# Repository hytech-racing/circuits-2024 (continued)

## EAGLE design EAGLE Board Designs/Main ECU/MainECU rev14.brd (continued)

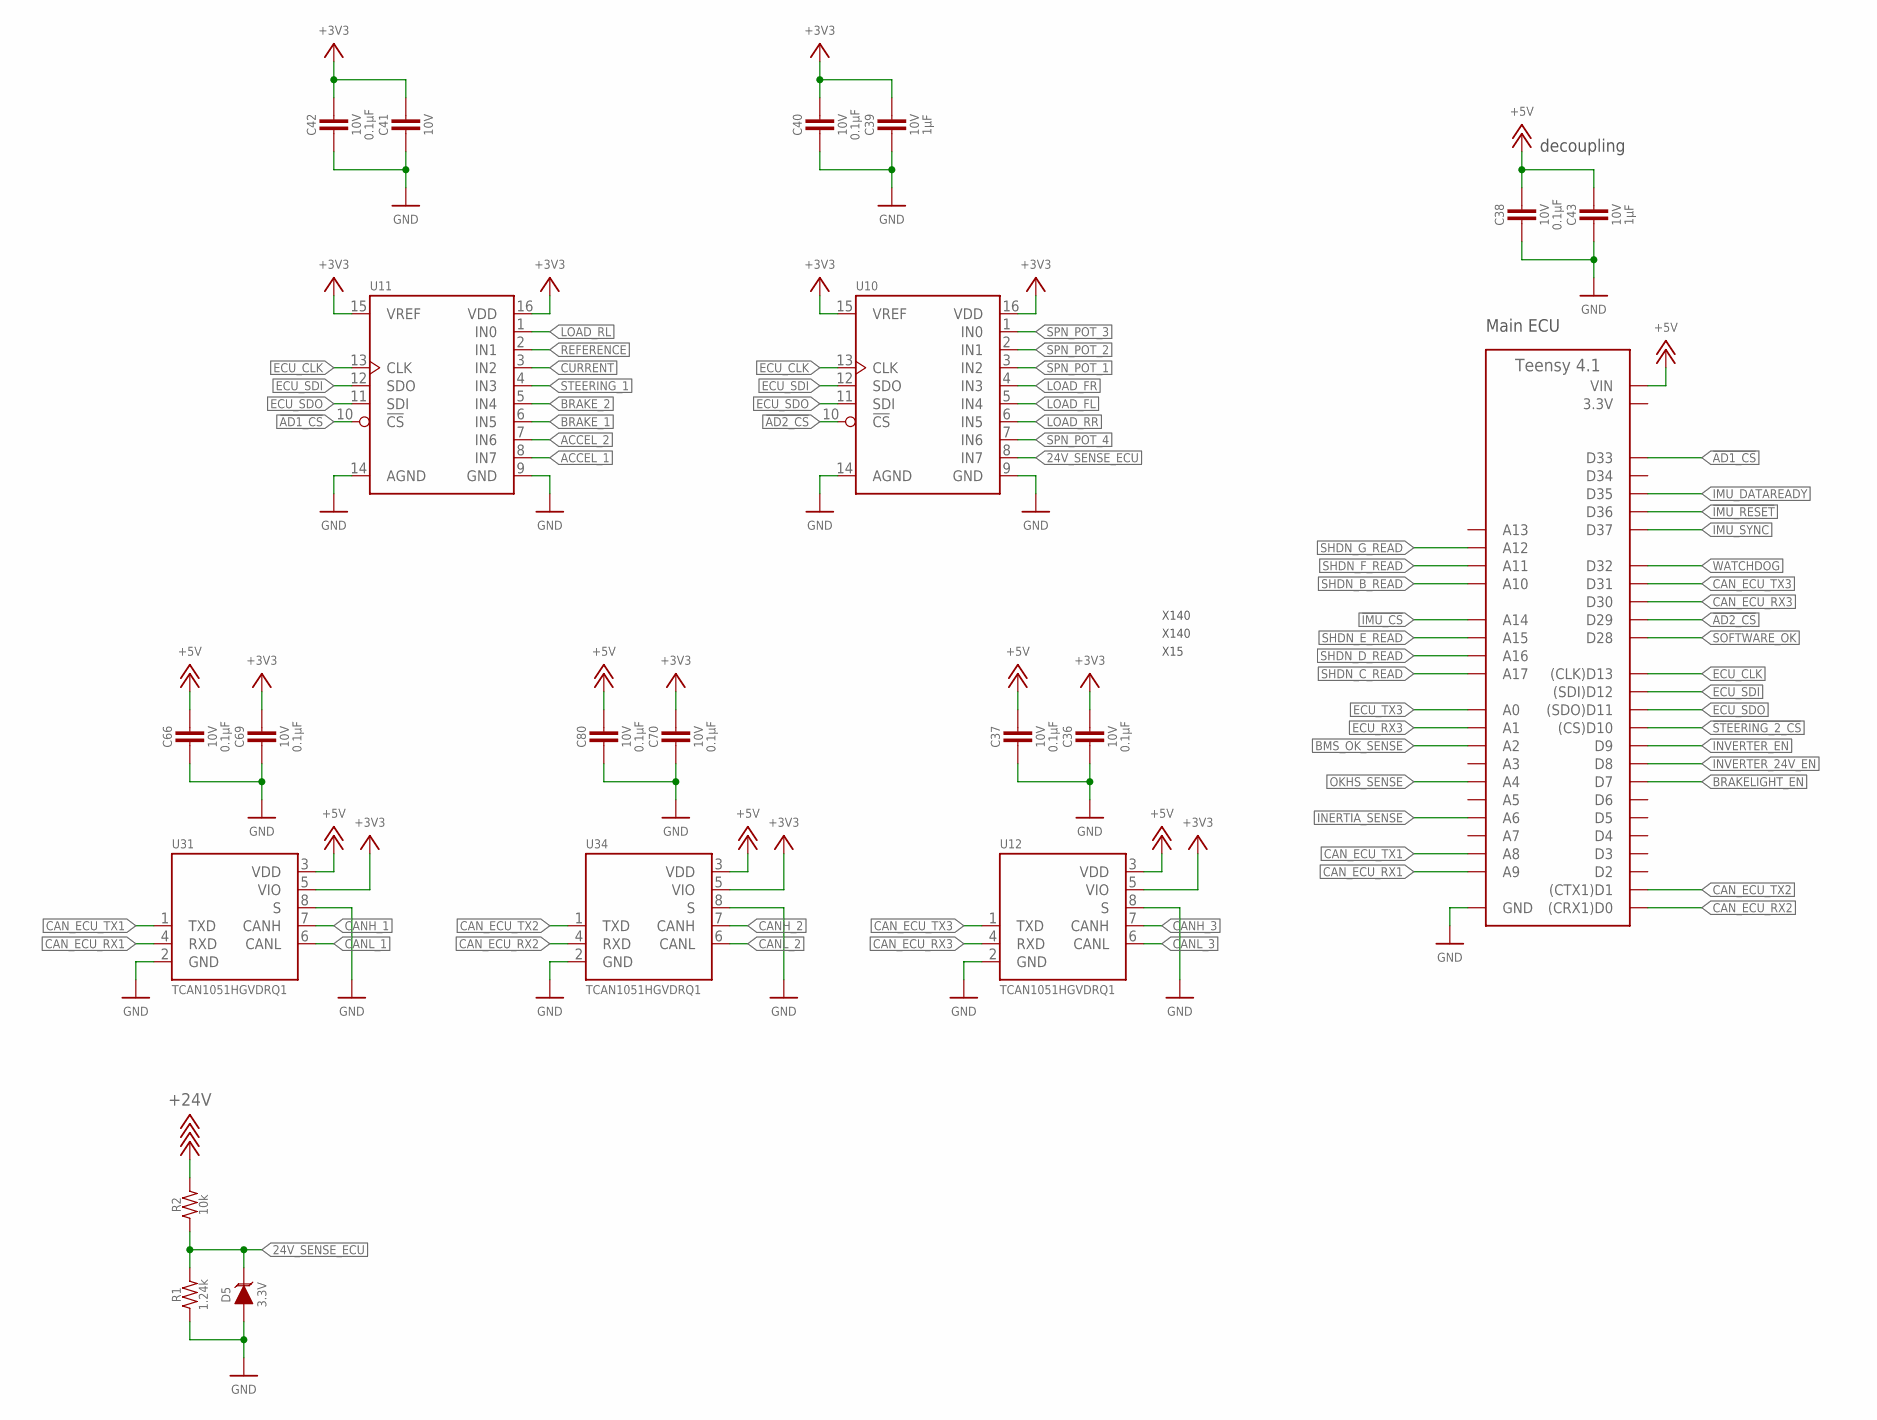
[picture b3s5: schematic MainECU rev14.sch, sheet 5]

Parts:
A2: TEENSY_4.1_SMT; TEENSY_LONG_SSM
C36, C37, C38, C40, C42, C66, C69, C70, C80: CAPACITOR_0603_10V_0.1UF; 0603-CAP
C39, C41, C43: CAPACITOR_0603_10V_1UF; 0603-CAP
D5: TVS__5V; SOT-23; VOLTAGE 3.3V; MPN GSOT03-E3-08
R1: RESISTOR_0603_1.24K; 0603-RES
R2: RESISTOR_0603_10K; 0603-RES
U10, U11: MCP3208; SOIC-16
U12, U31, U34: TCAN1051HQV-Q1; SOIC-08(NARROW,0.15")

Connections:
3.3V: A2.3.3V, A2.3.3V@1 (3.3V); also elsewhere on the board
24V_SENSE_ECU: D5.3 (C), R1.2, R2.1, U10.8 (IN7); also elsewhere on the board
!AD1_CS: A2.D33, U11.10 (!CS!)
!AD2_CS: A2.D29, U10.10 (!CS!)
!IMU_CS: A2.D38 (A14); also elsewhere on the board
!IMU_RESET: A2.D36; also elsewhere on the board
!STEERING_2_CS: A2.D10 ((CS)D10); also elsewhere on the board
+3V3: C36.1, C39.1, C40.1, C41.1, C42.1, C69.1, C70.1, U10.15 (VREF), U10.16 (VDD), U11.15 (VREF), U11.16 (VDD), U12.5 (VIO), U31.5 (VIO), U34.5 (VIO); also elsewhere on the board
+5V: A2.VIN, C37.1, C38.1, C43.1, C66.1, C80.1, U12.3 (VDD), U31.3 (VDD), U34.3 (VDD); also elsewhere on the board
+24V: R2.2; also elsewhere on the board
ACCEL_1: U11.8 (IN7); also elsewhere on the board
ACCEL_2: U11.7 (IN6); also elsewhere on the board
BMS_OK_SENSE: A2.D16 (A2); also elsewhere on the board
BRAKELIGHT_EN: A2.D7; also elsewhere on the board
BRAKE_1: U11.6 (IN5); also elsewhere on the board
BRAKE_2: U11.5 (IN4); also elsewhere on the board
CANH_1: U31.7 (CANH); also elsewhere on the board
CANH_2: U34.7 (CANH); also elsewhere on the board
CANH_3: U12.7 (CANH); also elsewhere on the board
CANL_1: U31.6 (CANL); also elsewhere on the board
CANL_2: U34.6 (CANL); also elsewhere on the board
CANL_3: U12.6 (CANL); also elsewhere on the board
CAN_ECU_RX1: A2.D23 (A9), U31.4 (RXD)
CAN_ECU_RX2: A2.D0 ((CRX1)D0), U34.4 (RXD)
CAN_ECU_RX3: A2.D30, U12.4 (RXD)
CAN_ECU_TX1: A2.D22 (A8), U31.1 (TXD)
CAN_ECU_TX2: A2.D1 ((CTX1)D1), U34.1 (TXD)
CAN_ECU_TX3: A2.D31, U12.1 (TXD)
CURRENT: U11.3 (IN2); also elsewhere on the board
ECU_CLK: A2.D13 ((CLK)D13), U10.13 (CLK), U11.13 (CLK); also elsewhere on the board
ECU_RX3: A2.D15 (A1); also elsewhere on the board
ECU_SDI: A2.D12 ((SDI)D12), U10.12 (SDO), U11.12 (SDO); also elsewhere on the board
ECU_SDO: A2.D11 ((SDO)D11), U10.11 (SDI), U11.11 (SDI); also elsewhere on the board
ECU_TX3: A2.D14 (A0); also elsewhere on the board
GND: A2.AGND/GND (GND), A2.GND, A2.GND@1 (GND), C36.2, C37.2, C38.2, C39.2, C40.2, C41.2, C42.2, C43.2, C66.2, C69.2, C70.2, C80.2, D5.1 (A), R1.1, U10.14 (AGND), U11.14 (AGND), U12.2 (GND), U12.8 (S), U31.2 (GND), U31.8 (S), U34.2 (GND), U34.8 (S); also elsewhere on the board
IMU_DATAREADY: A2.D35; also elsewhere on the board
IMU_SYNC: A2.D37; also elsewhere on the board
INERTIA_SENSE: A2.D20 (A6); also elsewhere on the board
INVERTER_24V_EN: A2.D8; also elsewhere on the board
INVERTER_EN: A2.D9; also elsewhere on the board
LOAD_FL: U10.5 (IN4); also elsewhere on the board
LOAD_FR: U10.4 (IN3); also elsewhere on the board
LOAD_RL: U11.1 (IN0); also elsewhere on the board
LOAD_RR: U10.6 (IN5); also elsewhere on the board
OKHS_SENSE: A2.D18 (A4); also elsewhere on the board
REFERENCE: U11.2 (IN1); also elsewhere on the board
SHDN_B_READ: A2.D24 (A10); also elsewhere on the board
SHDN_C_READ: A2.D41 (A17); also elsewhere on the board
SHDN_D_READ: A2.D40 (A16); also elsewhere on the board
SHDN_E_READ: A2.D39 (A15); also elsewhere on the board
SHDN_F_READ: A2.D25 (A11); also elsewhere on the board
SHDN_G_READ: A2.D26 (A12); also elsewhere on the board
SOFTWARE_OK: A2.D28; also elsewhere on the board
SPN_POT_1: U10.3 (IN2); also elsewhere on the board
SPN_POT_2: U10.2 (IN1); also elsewhere on the board
SPN_POT_3: U10.1 (IN0); also elsewhere on the board
SPN_POT_4: U10.7 (IN6); also elsewhere on the board
STEERING_1: U11.4 (IN3); also elsewhere on the board
WATCHDOG: A2.D32; also elsewhere on the board

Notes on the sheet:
decoupling
Main ECU
X15
X140

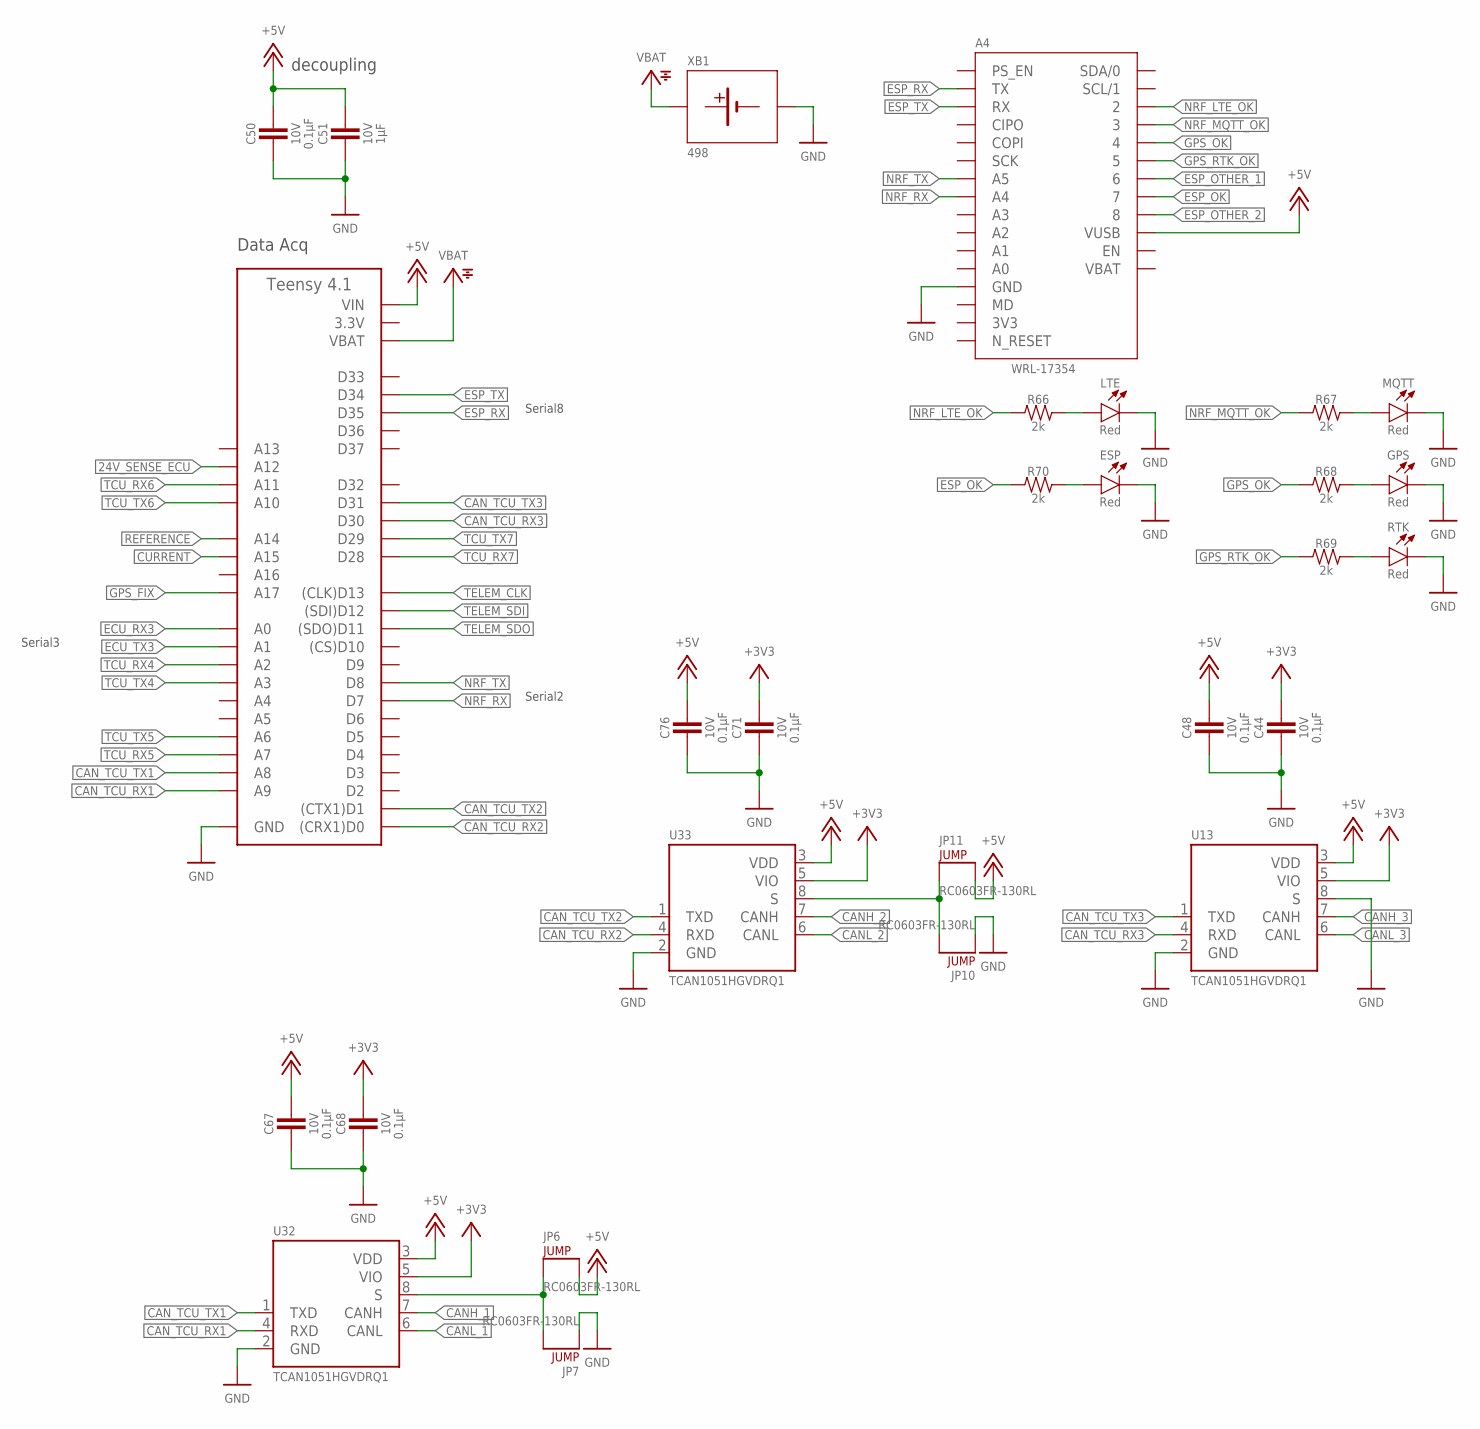
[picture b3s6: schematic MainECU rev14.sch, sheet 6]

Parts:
A3: TEENSY_4.1; TEENSY_LONG_EXT
A4: NRF9160LTE
C44, C48, C50, C67, C68, C71, C76: CAPACITOR_0603_10V_0.1UF; 0603-CAP
C51: CAPACITOR_0603_10V_1UF; 0603-CAP
ESP: LED_0603_RED; 0603-LED
GPS: LED_0603_RED; 0603-LED
JP6, JP11: JUMPER_0603_; 0603-RES
JP7, JP10: DNP; 0603-RES
LTE: LED_0603_RED; 0603-LED
MQTT: LED_0603_RED; 0603-LED
R66, R67, R68, R69, R70: RESISTOR_0603_2K; 0603-RES
RTK: LED_0603_RED; 0603-LED
U13, U32, U33: TCAN1051HQV-Q1; SOIC-08(NARROW,0.15")
XB1: BATTERY_HOLDER_KEYSTONE_498; 498

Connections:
3.3V: A3.3V3 (3.3V), A3.3V3@2 (3.3V), A3.3V3@3 (3.3V); also elsewhere on the board
3V3: A4.3V3
24V_SENSE_ECU: A3.D26 (A12); also elsewhere on the board
+3V3: C44.1, C68.1, C71.1, U13.5 (VIO), U32.5 (VIO), U33.5 (VIO); also elsewhere on the board
+5V: A3.VIN, A4.VUSB, C48.1, C50.1, C51.1, C67.1, C76.1, JP6.2, JP11.2, U13.3 (VDD), U32.3 (VDD), U33.3 (VDD); also elsewhere on the board
CANH_1: U32.7 (CANH); also elsewhere on the board
CANH_2: U33.7 (CANH); also elsewhere on the board
CANH_3: U13.7 (CANH); also elsewhere on the board
CANL_1: U32.6 (CANL); also elsewhere on the board
CANL_2: U33.6 (CANL); also elsewhere on the board
CANL_3: U13.6 (CANL); also elsewhere on the board
CAN_TCU_RX1: A3.D23 (A9), U32.4 (RXD)
CAN_TCU_RX2: A3.D0 ((CRX1)D0), U33.4 (RXD)
CAN_TCU_RX3: A3.D30, U13.4 (RXD)
CAN_TCU_TX1: A3.D22 (A8), U32.1 (TXD)
CAN_TCU_TX2: A3.D1 ((CTX1)D1), U33.1 (TXD)
CAN_TCU_TX3: A3.D31, U13.1 (TXD)
CURRENT: A3.D39 (A15); also elsewhere on the board
ECU_RX3: A3.D14 (A0); also elsewhere on the board
ECU_TX3: A3.D15 (A1); also elsewhere on the board
ESP_OK: A4.7, R70.1
ESP_OTHER_1: A4.6
ESP_OTHER_2: A4.8
ESP_RX: A3.D35, A4.TX
ESP_TX: A3.D34, A4.RX
GND: A3.AGND/GND (GND), A3.GND, A3.GND@2 (GND), A4.GND, C44.2, C48.2, C50.2, C51.2, C67.2, C68.2, C71.2, C76.2, ESP.1 (C), GPS.1 (C), JP7.1, JP10.1, LTE.1 (C), MQTT.1 (C), RTK.1 (C), U13.2 (GND), U13.8 (S), U32.2 (GND), U33.2 (GND), XB1.2 (MINUS); also elsewhere on the board
GPS_FIX: A3.D41 (A17)
GPS_OK: A4.4, R68.1
GPS_RTK_OK: A4.5, R69.1
unnamed: JP6.1, JP7.2, U32.8 (S)
unnamed: JP10.2, JP11.1, U33.8 (S)
unnamed: ESP.2 (A), R70.2
unnamed: LTE.2 (A), R66.2
unnamed: MQTT.2 (A), R67.2
unnamed: GPS.2 (A), R68.2
unnamed: R69.2, RTK.2 (A)
NRF_LTE_OK: A4.2, R66.1
NRF_MQTT_OK: A4.3, R67.1
NRF_RX: A3.D7, A4.A4
NRF_TX: A3.D8, A4.A5
REFERENCE: A3.D38 (A14); also elsewhere on the board
TCU_RX4: A3.D16 (A2)
TCU_RX5: A3.D21 (A7)
TCU_RX6: A3.D25 (A11)
TCU_RX7: A3.D28
TCU_TX4: A3.D17 (A3)
TCU_TX5: A3.D20 (A6)
TCU_TX6: A3.D24 (A10)
TCU_TX7: A3.D29
TELEM_CLK: A3.D13 ((CLK)D13)
TELEM_SDI: A3.D12 ((SDI)D12)
TELEM_SDO: A3.D11 ((SDO)D11)
VBAT: A3.VBAT, A4.VBAT, XB1.1 (PLUS)

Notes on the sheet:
decoupling
Data Acq
Serial2
Serial3
Serial8

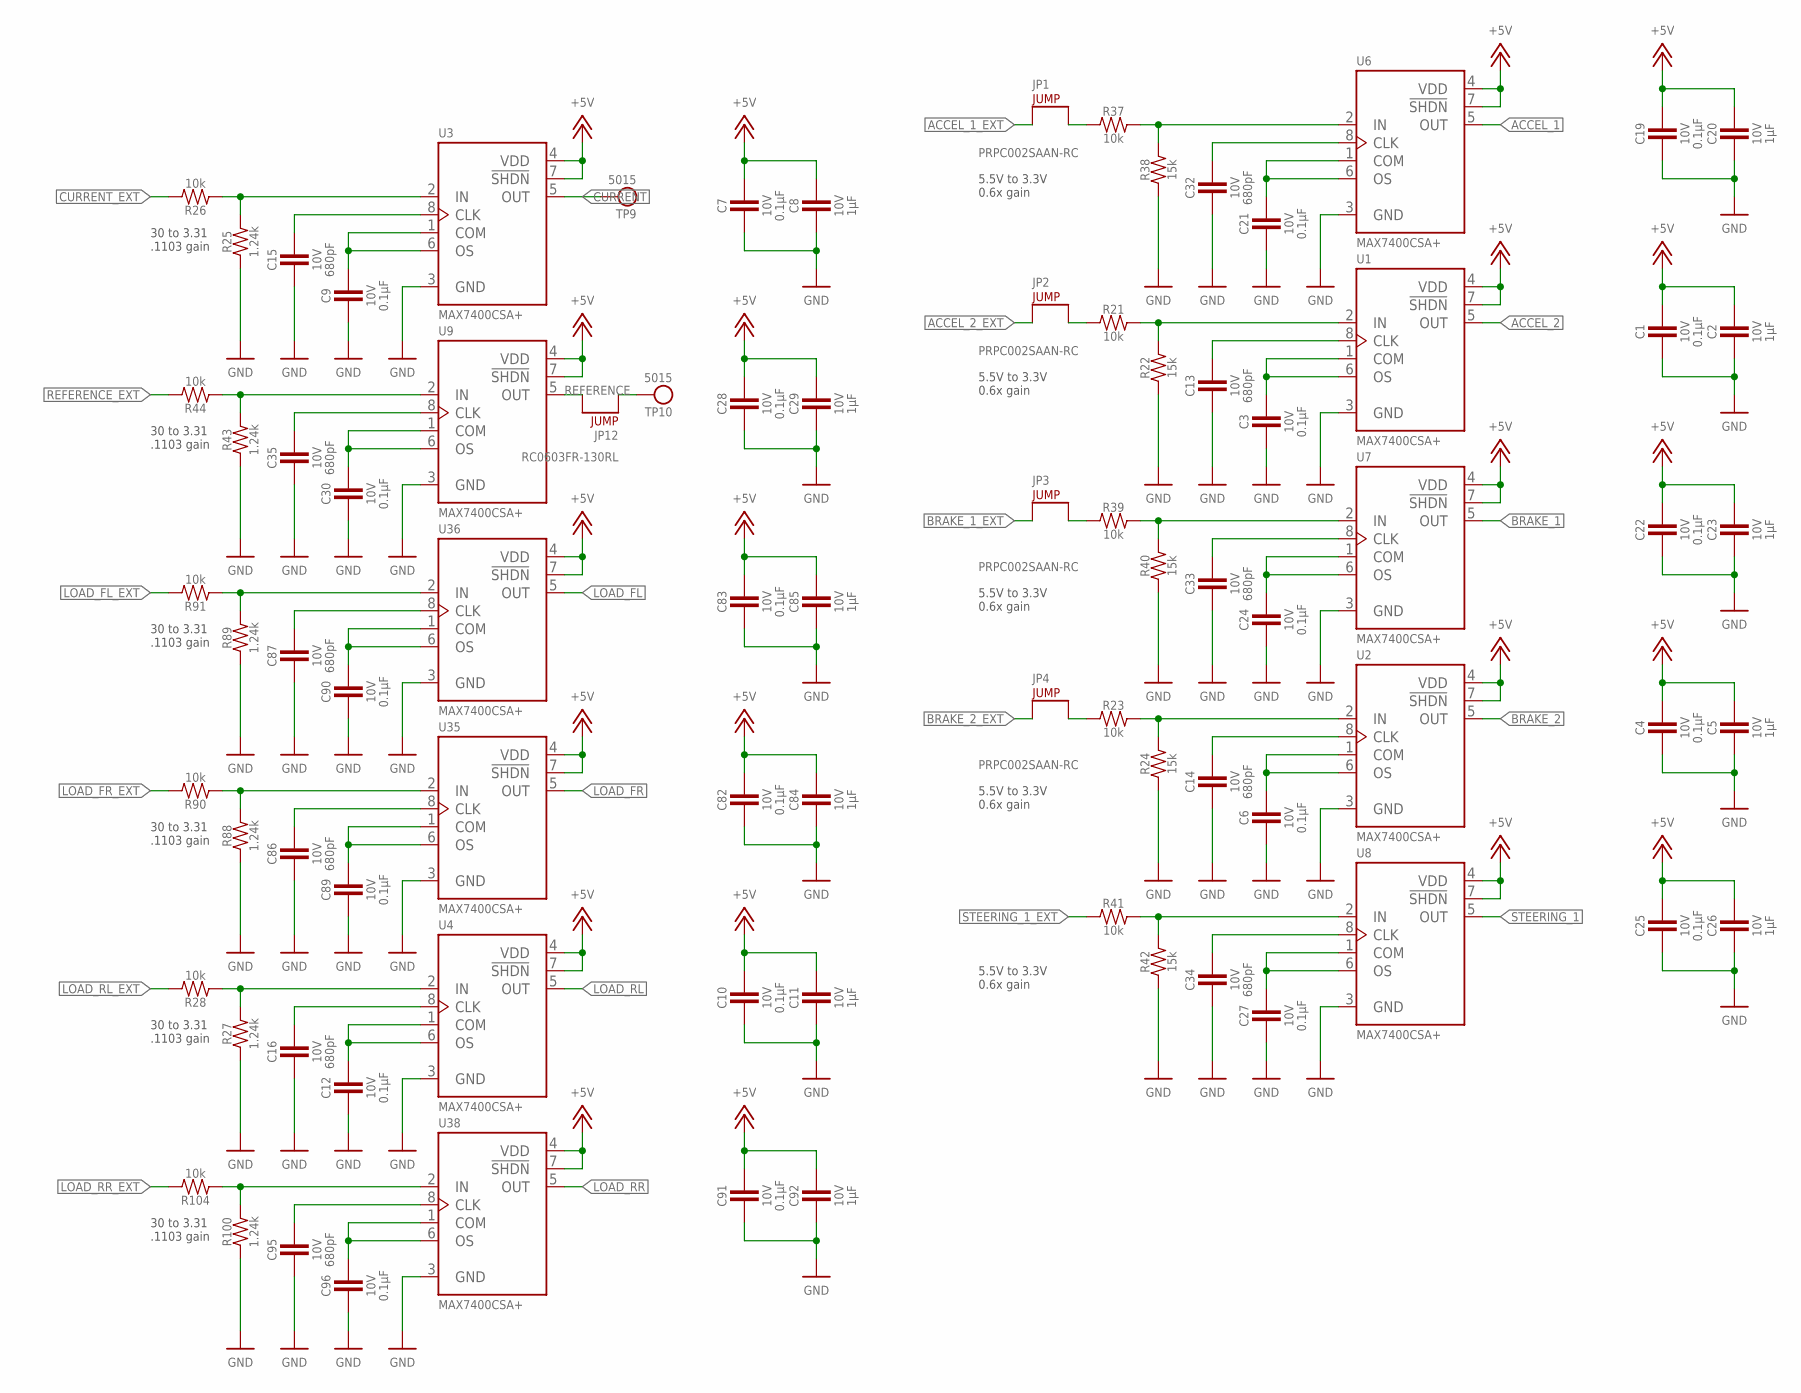
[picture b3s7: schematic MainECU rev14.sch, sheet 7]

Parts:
C1, C3, C4, C6, C7, C9, C10, C12, C19, C21, C22, C24, C25, C27, C28, C30, C82, C83, C89, C90, C91, C96: CAPACITOR_0603_10V_0.1UF; 0603-CAP
C2, C5, C8, C11, C20, C23, C26, C29, C84, C85, C92: CAPACITOR_0603_10V_1UF; 0603-CAP
C13, C14, C15, C16, C32, C33, C34, C35, C86, C87, C95: CAPACITOR_0603_10V_680PF; 0603-CAP
JP1, JP2, JP3, JP4: JUMPER__1X02; 1X02
JP12: JUMPER_0603_; 0603-RES
R21, R23, R26, R28, R37, R39, R41, R44, R90, R91, R104: RESISTOR_0603_10K; 0603-RES
R22, R24, R38, R40, R42: RESISTOR_0603_15K; 0603-RES
R25, R27, R43, R88, R89, R100: RESISTOR_0603_1.24K; 0603-RES
TP9, TP10: TEST_POINT; 5015
U1, U2, U3, U4, U6, U7, U8, U9, U35, U36, U38: MAX7400; SOIC-08(NARROW,0.15")

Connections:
+5V: C1.1, C2.1, C4.1, C5.1, C7.1, C8.1, C10.1, C11.1, C19.1, C20.1, C22.1, C23.1, C25.1, C26.1, C28.1, C29.1, C82.1, C83.1, C84.1, C85.1, C91.1, C92.1, U1.4 (VDD), U1.7 (!SHDN), U2.4 (VDD), U2.7 (!SHDN), U3.4 (VDD), U3.7 (!SHDN), U4.4 (VDD), U4.7 (!SHDN), U6.4 (VDD), U6.7 (!SHDN), U7.4 (VDD), U7.7 (!SHDN), U8.4 (VDD), U8.7 (!SHDN), U9.4 (VDD), U9.7 (!SHDN), U35.4 (VDD), U35.7 (!SHDN), U36.4 (VDD), U36.7 (!SHDN), U38.4 (VDD), U38.7 (!SHDN); also elsewhere on the board
ACCEL_1: U6.5 (OUT); also elsewhere on the board
ACCEL_1_EXT: JP1.1; also elsewhere on the board
ACCEL_1_PRE: R37.2, R38.2, U6.2 (IN)
ACCEL_2: U1.5 (OUT); also elsewhere on the board
ACCEL_2_EXT: JP2.1; also elsewhere on the board
ACCEL_2_PRE: R21.2, R22.2, U1.2 (IN)
BRAKE_1: U7.5 (OUT); also elsewhere on the board
BRAKE_1_EXT: JP3.1; also elsewhere on the board
BRAKE_1_PRE: R39.2, R40.2, U7.2 (IN)
BRAKE_2: U2.5 (OUT); also elsewhere on the board
BRAKE_2_EXT: JP4.1; also elsewhere on the board
BRAKE_2_PRE: R23.2, R24.2, U2.2 (IN)
CURRENT: TP9.1, U3.5 (OUT); also elsewhere on the board
CURRENT_EXT: R26.2; also elsewhere on the board
GND: C1.2, C2.2, C3.2, C4.2, C5.2, C6.2, C7.2, C8.2, C9.2, C10.2, C11.2, C12.2, C13.2, C14.2, C15.2, C16.2, C19.2, C20.2, C21.2, C22.2, C23.2, C24.2, C25.2, C26.2, C27.2, C28.2, C29.2, C30.2, C32.2, C33.2, C34.2, C35.2, C82.2, C83.2, C84.2, C85.2, C86.2, C87.2, C89.2, C90.2, C91.2, C92.2, C95.2, C96.2, R22.1, R24.1, R25.1, R27.1, R38.1, R40.1, R42.1, R43.1, R88.1, R89.1, R100.1, U1.3 (GND), U2.3 (GND), U3.3 (GND), U4.3 (GND), U6.3 (GND), U7.3 (GND), U8.3 (GND), U9.3 (GND), U35.3 (GND), U36.3 (GND), U38.3 (GND); also elsewhere on the board
LOAD_FL: U36.5 (OUT); also elsewhere on the board
LOAD_FL_EXT: R91.2; also elsewhere on the board
LOAD_FR: U35.5 (OUT); also elsewhere on the board
LOAD_FR_EXT: R90.2; also elsewhere on the board
LOAD_RL: U4.5 (OUT); also elsewhere on the board
LOAD_RL_EXT: R28.2; also elsewhere on the board
LOAD_RR: U38.5 (OUT); also elsewhere on the board
LOAD_RR_EXT: R104.2; also elsewhere on the board
unnamed: JP1.2, R37.1
unnamed: JP2.2, R21.1
unnamed: JP4.2, R23.1
unnamed: JP3.2, R39.1
unnamed: JP12.2, U9.5 (OUT)
unnamed: R25.2, R26.1, U3.2 (IN)
unnamed: C9.1, U3.1 (COM), U3.6 (OS)
unnamed: C15.1, U3.8 (CLK)
unnamed: R43.2, R44.1, U9.2 (IN)
unnamed: C30.1, U9.1 (COM), U9.6 (OS)
unnamed: C35.1, U9.8 (CLK)
unnamed: R89.2, R91.1, U36.2 (IN)
unnamed: C90.1, U36.1 (COM), U36.6 (OS)
unnamed: C87.1, U36.8 (CLK)
unnamed: R88.2, R90.1, U35.2 (IN)
unnamed: C89.1, U35.1 (COM), U35.6 (OS)
unnamed: C86.1, U35.8 (CLK)
unnamed: R27.2, R28.1, U4.2 (IN)
unnamed: C12.1, U4.1 (COM), U4.6 (OS)
unnamed: C16.1, U4.8 (CLK)
unnamed: R100.2, R104.1, U38.2 (IN)
unnamed: C96.1, U38.1 (COM), U38.6 (OS)
unnamed: C95.1, U38.8 (CLK)
unnamed: C27.1, U8.1 (COM), U8.6 (OS)
unnamed: C21.1, U6.1 (COM), U6.6 (OS)
unnamed: C32.1, U6.8 (CLK)
unnamed: C34.1, U8.8 (CLK)
unnamed: C3.1, U1.1 (COM), U1.6 (OS)
unnamed: C13.1, U1.8 (CLK)
unnamed: C24.1, U7.1 (COM), U7.6 (OS)
unnamed: C33.1, U7.8 (CLK)
unnamed: C6.1, U2.1 (COM), U2.6 (OS)
unnamed: C14.1, U2.8 (CLK)
REFERENCE: JP12.1, TP10.1; also elsewhere on the board
REFERENCE_EXT: R44.2; also elsewhere on the board
STEERING_1: U8.5 (OUT); also elsewhere on the board
STEERING_1_EXT: R41.1; also elsewhere on the board
STEERING_1_PRE: R41.2, R42.2, U8.2 (IN)

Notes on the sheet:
30 to 3.31 .1103 gain
5.5V to 3.3V 0.6x gain

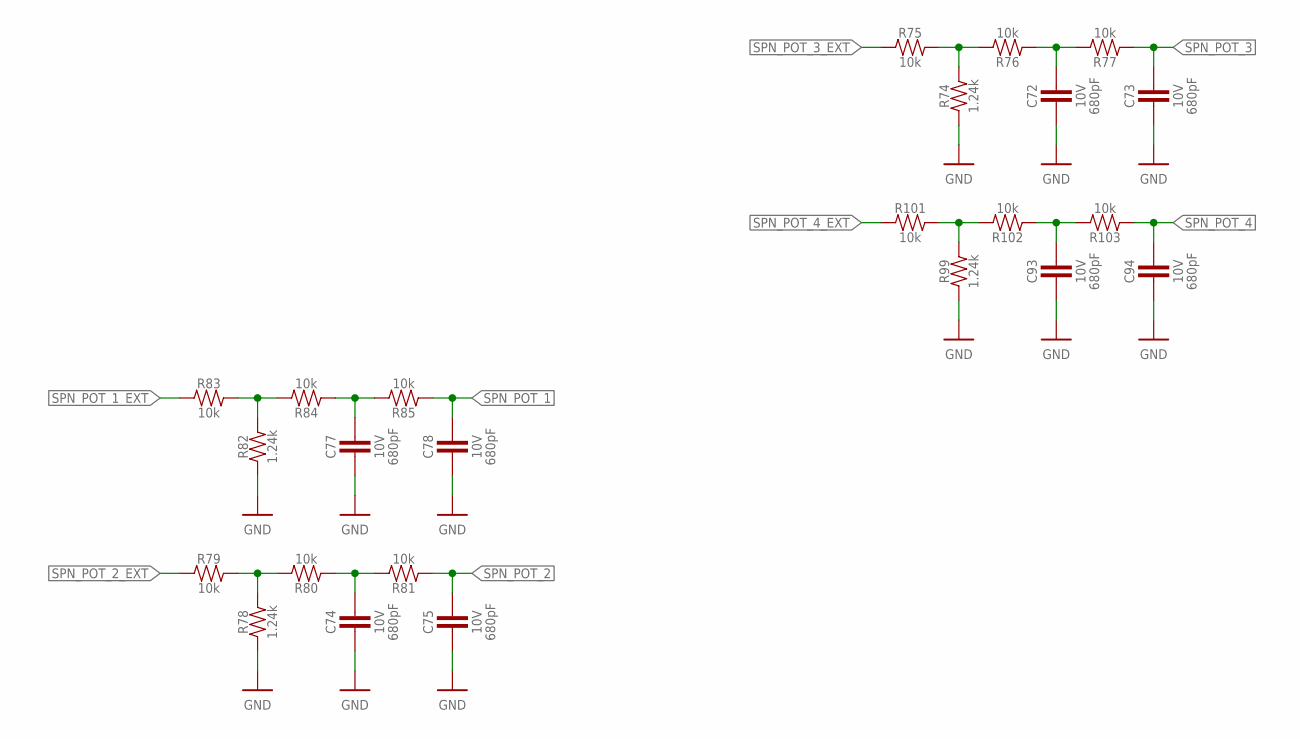
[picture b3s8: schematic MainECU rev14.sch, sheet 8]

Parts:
C72, C73, C74, C75, C77, C78, C93, C94: CAPACITOR_0603_10V_680PF; 0603-CAP
R74, R78, R82, R99: RESISTOR_0603_1.24K; 0603-RES
R75, R76, R77, R79, R80, R81, R83, R84, R85, R101, R102, R103: RESISTOR_0603_10K; 0603-RES

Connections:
GND: C72.2, C73.2, C74.2, C75.2, C77.2, C78.2, C93.2, C94.2, R74.1, R78.1, R82.1, R99.1; also elsewhere on the board
unnamed: R82.2, R83.2, R84.2
unnamed: C77.1, R84.1, R85.2
unnamed: R78.2, R79.2, R80.2
unnamed: C74.1, R80.1, R81.2
unnamed: R74.2, R75.2, R76.2
unnamed: C72.1, R76.1, R77.2
unnamed: R99.2, R101.2, R102.2
unnamed: C93.1, R102.1, R103.2
SPN_POT_1: C78.1, R85.1; also elsewhere on the board
SPN_POT_1_EXT: R83.1; also elsewhere on the board
SPN_POT_2: C75.1, R81.1; also elsewhere on the board
SPN_POT_2_EXT: R79.1; also elsewhere on the board
SPN_POT_3: C73.1, R77.1; also elsewhere on the board
SPN_POT_3_EXT: R75.1; also elsewhere on the board
SPN_POT_4: C94.1, R103.1; also elsewhere on the board
SPN_POT_4_EXT: R101.1; also elsewhere on the board

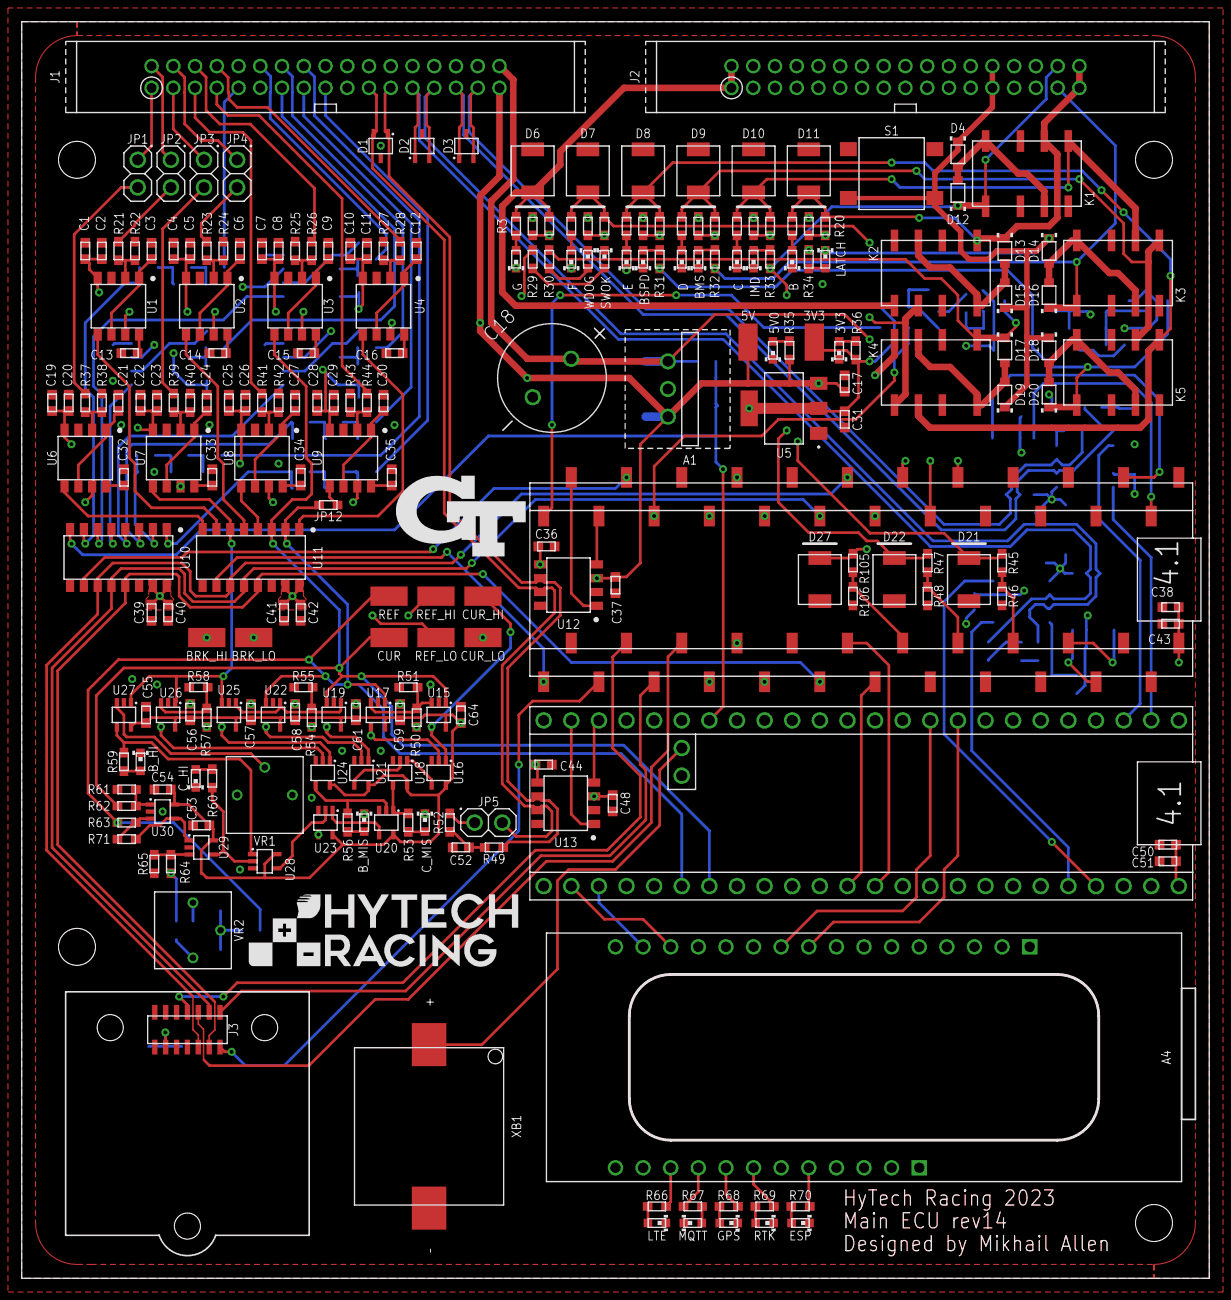
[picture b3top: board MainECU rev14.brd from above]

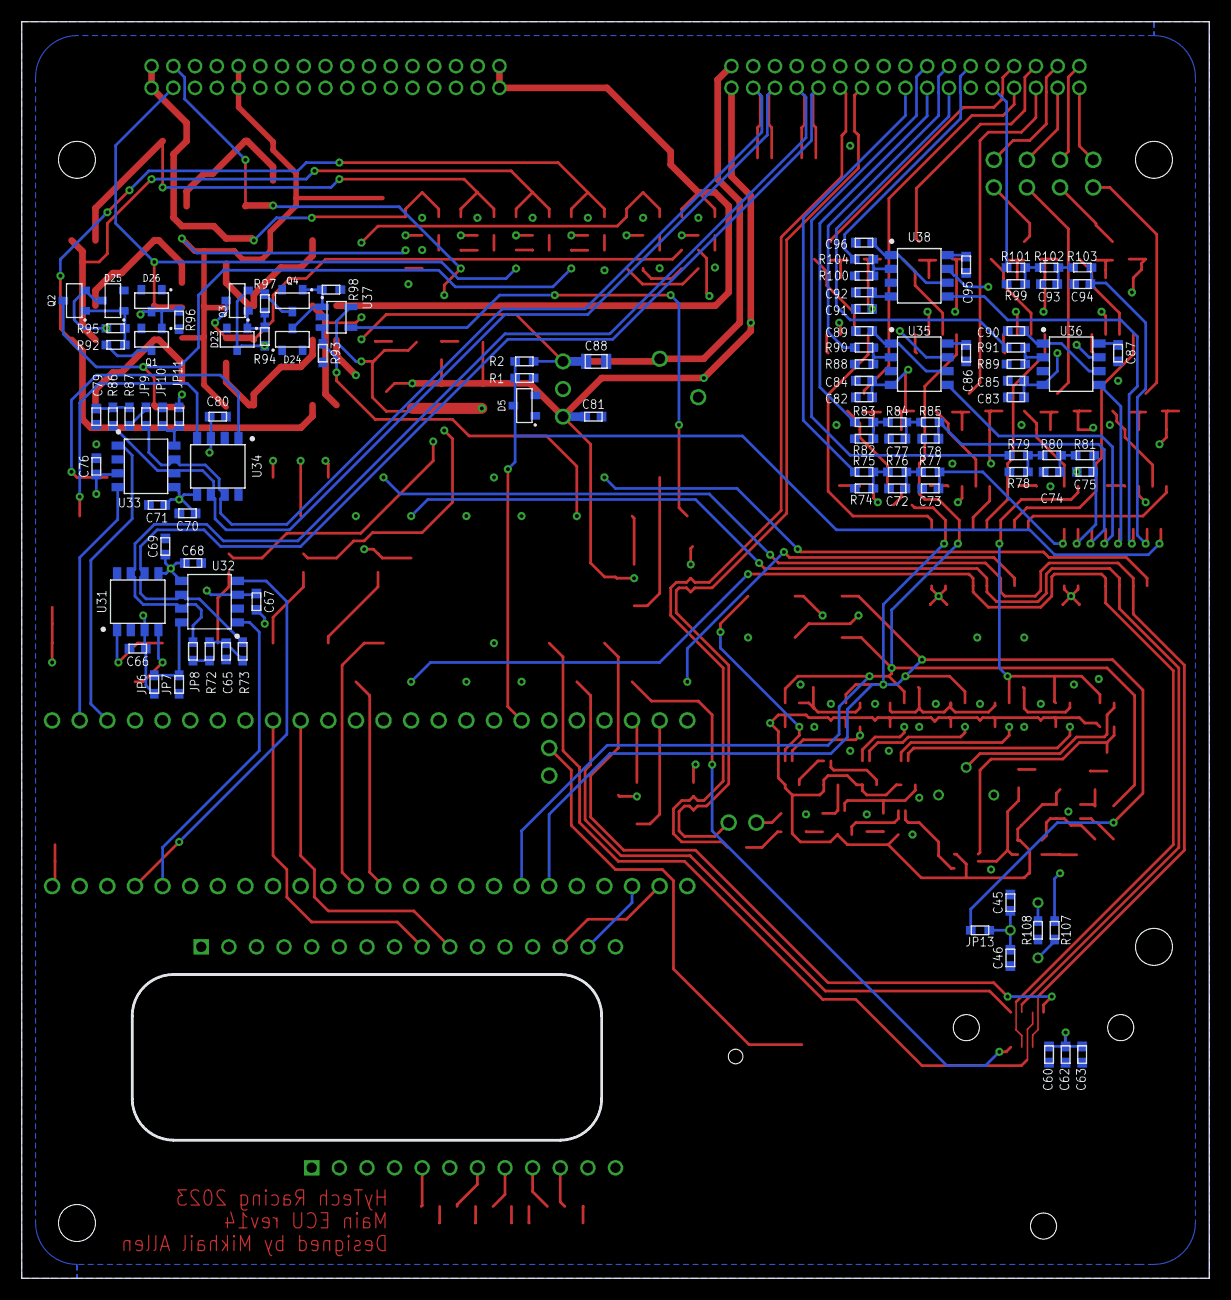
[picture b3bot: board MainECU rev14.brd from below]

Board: 4 copper layers, 109.2 x 115.6 mm, 338 parts (98 on the bottom side), 215 nets.

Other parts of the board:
$$U$1: LOGO_GT_MEDIUM
$$U$2, $$U$6: MOUNTING_M3
U$3, U$5: MOUNTING_M3
U$6: LOGO_HYTECH_MEDIUM

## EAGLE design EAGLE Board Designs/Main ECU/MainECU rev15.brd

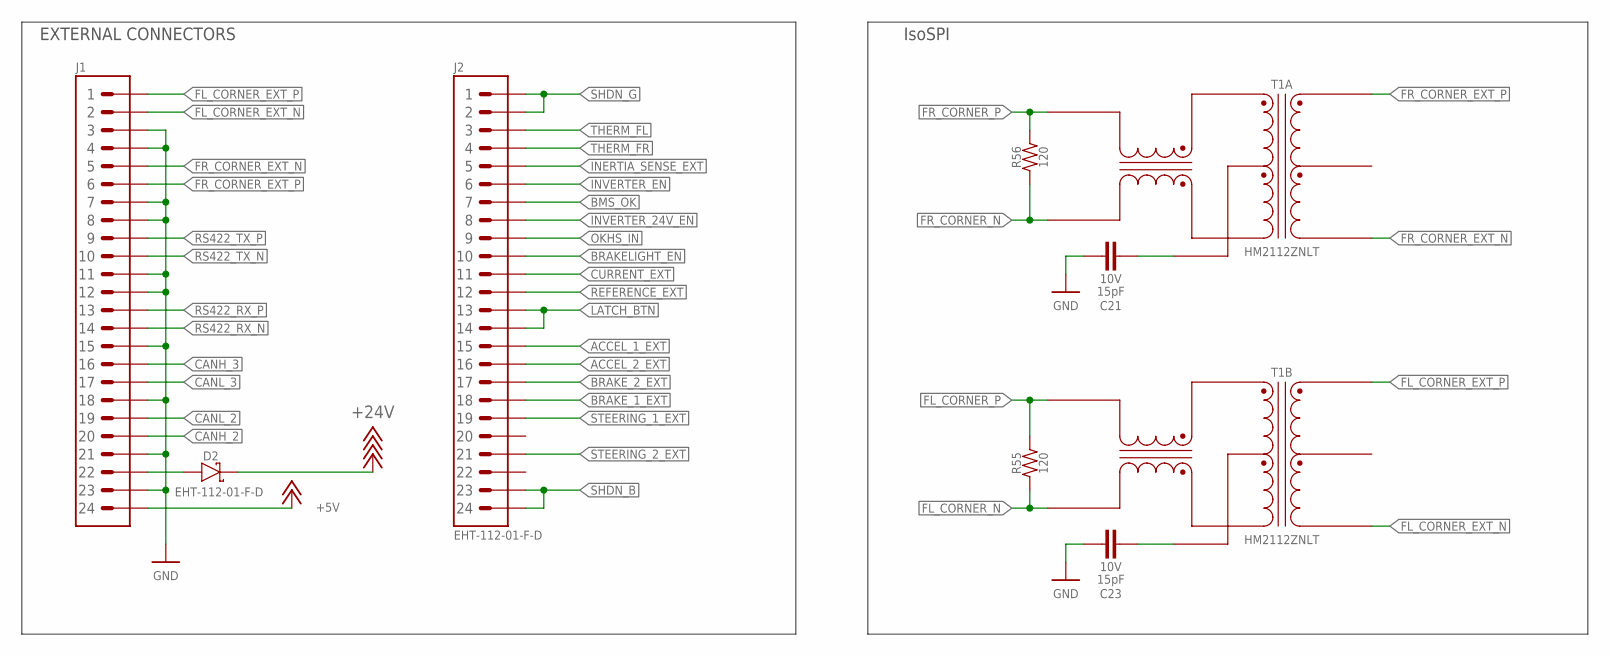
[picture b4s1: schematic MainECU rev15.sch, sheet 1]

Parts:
C21, C23: CAPACITOR_0603_10V_15PF; 0603-CAP
D2: SCHOTTKY_1206_40V; 1206-DIODE
J1, J2: CONNECTOR-24_CONNECTOR-24_; EHT-112-01
R55, R56: RESISTOR_0603_120; 0603-RES
T1: TRANSFORMER_HM2112ZNLT; HM2112ZNLT

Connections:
+5V: J1.24; also elsewhere on the board
+24V: D2.2 (C); also elsewhere on the board
ACCEL_1_EXT: J2.15; also elsewhere on the board
ACCEL_2_EXT: J2.16; also elsewhere on the board
BMS_OK: J2.7; also elsewhere on the board
BRAKELIGHT_EN: J2.10; also elsewhere on the board
BRAKE_1_EXT: J2.18; also elsewhere on the board
BRAKE_2_EXT: J2.17; also elsewhere on the board
CANH_2: J1.20; also elsewhere on the board
CANH_3: J1.16; also elsewhere on the board
CANL_2: J1.19; also elsewhere on the board
CANL_3: J1.17; also elsewhere on the board
CURRENT_EXT: J2.11; also elsewhere on the board
FL_CORNER_EXT_N: J1.2, T1.6 (MX-)
FL_CORNER_EXT_P: J1.1, T1.4 (MX+)
FL_CORNER_N: R55.1, T1.7 (TD-); also elsewhere on the board
FL_CORNER_P: R55.2, T1.9 (TD+); also elsewhere on the board
FR_CORNER_EXT_N: J1.5, T1.3 (MX-)
FR_CORNER_EXT_P: J1.6, T1.1 (MX+)
FR_CORNER_N: R56.1, T1.10 (TD-); also elsewhere on the board
FR_CORNER_P: R56.2, T1.12 (TD+); also elsewhere on the board
GND: C21.2, C23.2, J1.3, J1.4, J1.7, J1.8, J1.11, J1.12, J1.15, J1.18, J1.21, J1.23; also elsewhere on the board
INERTIA_SENSE_EXT: J2.5; also elsewhere on the board
INVERTER_24V_EN: J2.8; also elsewhere on the board
INVERTER_EN: J2.6; also elsewhere on the board
LATCH_BTN: J2.13, J2.14; also elsewhere on the board
unnamed: C21.1, T1.11 (TCT)
unnamed: C23.1, T1.8 (TCT)
unnamed: D2.1 (A), J1.22
OKHS_IN: J2.9; also elsewhere on the board
REFERENCE_EXT: J2.12; also elsewhere on the board
RS422_RX_N: J1.14; also elsewhere on the board
RS422_RX_P: J1.13; also elsewhere on the board
RS422_TX_N: J1.10; also elsewhere on the board
RS422_TX_P: J1.9; also elsewhere on the board
SHDN_B: J2.23, J2.24; also elsewhere on the board
SHDN_G: J2.1, J2.2; also elsewhere on the board
STEERING_1_EXT: J2.19; also elsewhere on the board
STEERING_2_EXT: J2.21; also elsewhere on the board
THERM_FL: J2.3; also elsewhere on the board
THERM_FR: J2.4; also elsewhere on the board

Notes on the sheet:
EXTERNAL CONNECTORS
IsoSPI
